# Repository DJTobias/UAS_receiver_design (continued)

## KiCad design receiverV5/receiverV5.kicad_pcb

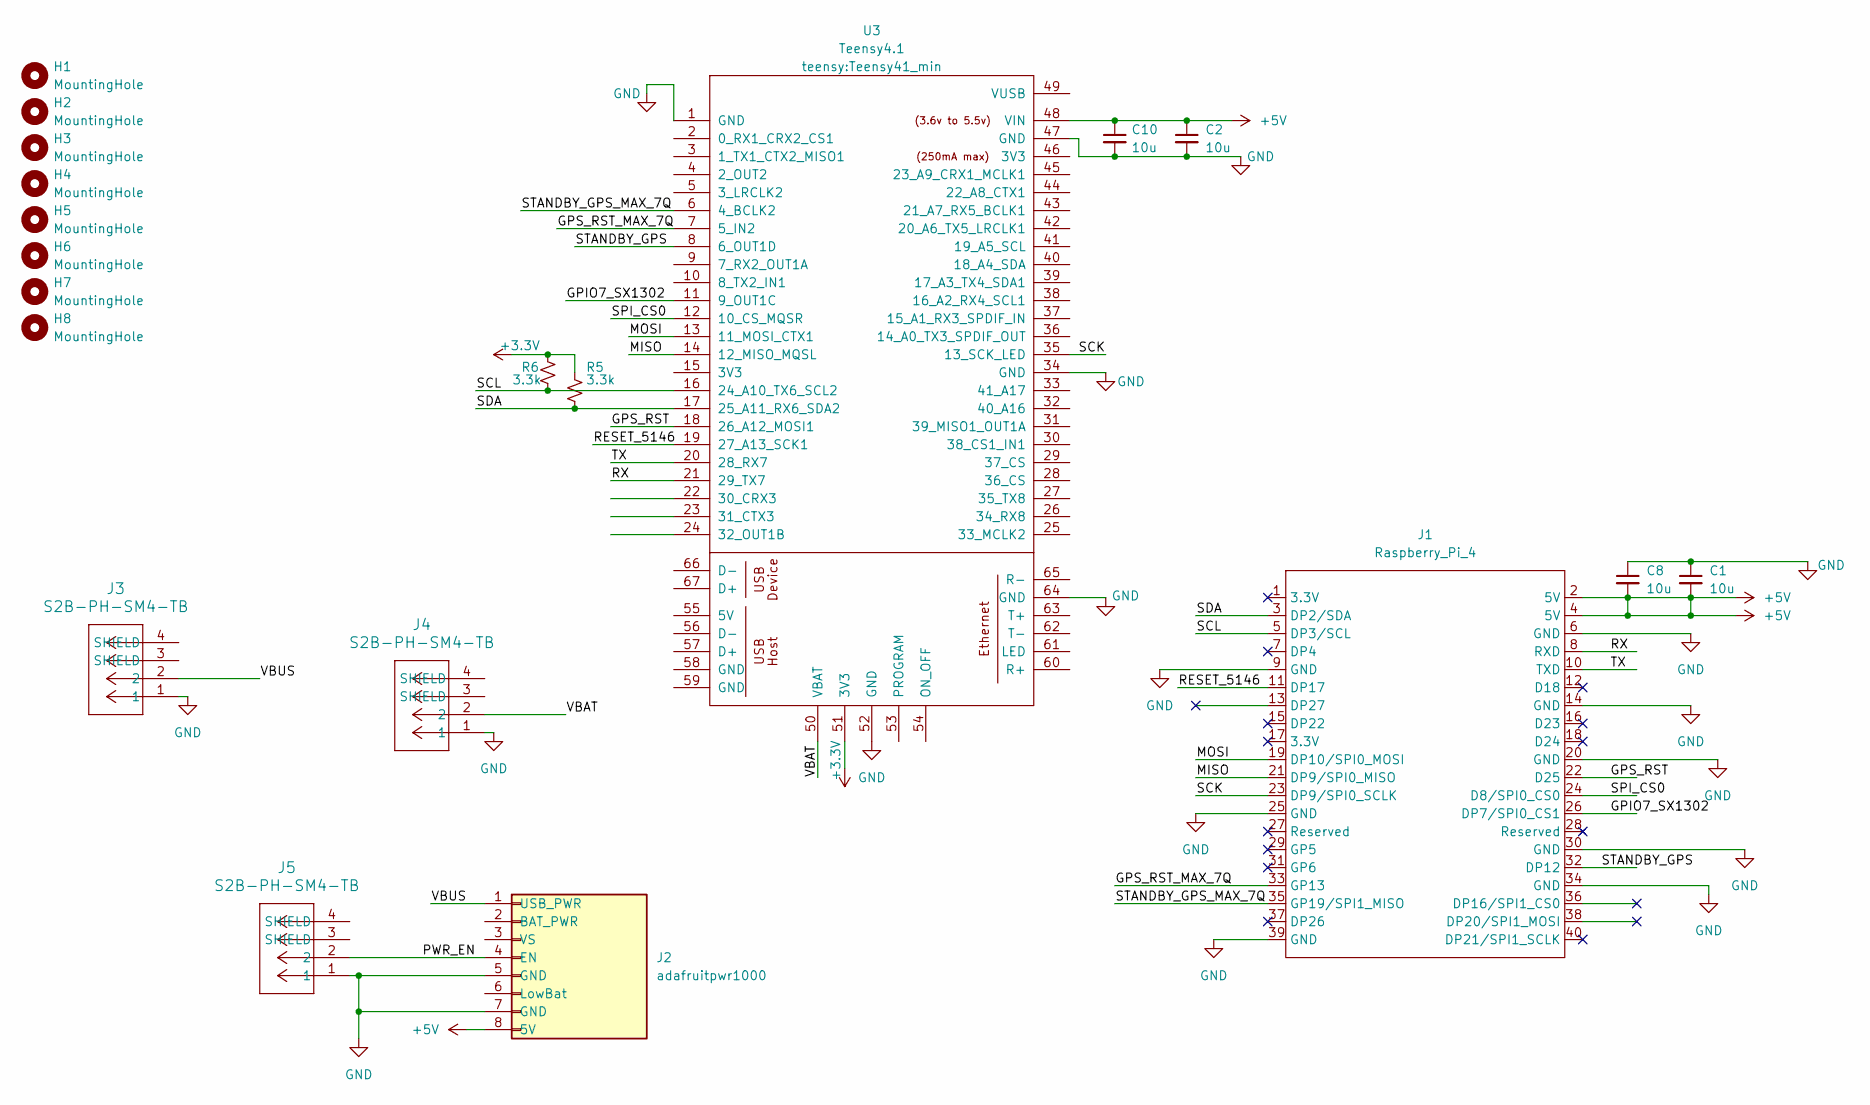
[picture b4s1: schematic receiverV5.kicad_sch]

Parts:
C1, C2, C8, C10: 10u; C_1206_3216Metric_Pad1.33x1.80mm_HandSolder
H1, H2, H3, H4: MountingHole; mountinghole3mm
H5: MountingHole; MountingHole_4mm_t4
H6, H7, H8: MountingHole; mountinghole4mm
J1: Raspberry_Pi_4; PinHeader_2x20_P2.54mm_Vertical
J2: adafruitpwr1000; adafruit powerboost 1000
J3, J4, J5: S2B-PH-SM4-TB; CONN_S2B-PH-SM4-TB_JST_mod2
R5, R6: 3.3k; R_1206_3216Metric_Pad1.30x1.75mm_HandSolder
U3: Teensy4.1; Teensy41_min

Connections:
+3.3V: R5.1, R6.1, U3.51 (3V3)
+5V: C1.2, C2.1, C8.2, C10.1, J1.2 (5V), J1.4 (5V), J2.8 (5V), U3.48 (VIN)
/GPIO7_SX1302: J1.26 (DP7/SPI0_CS1), U3.11 (9_OUT1C)
/GPS_RST: J1.22 (D25), U3.18 (26_A12_MOSI1)
/GPS_RST_MAX_7Q: J1.33 (GP13), U3.7 (5_IN2)
/MISO: J1.21 (DP9/SPI0_MISO), U3.14 (12_MISO_MQSL)
/MOSI: J1.19 (DP10/SPI0_MOSI), U3.13 (11_MOSI_CTX1)
/PWR_EN: J2.4 (EN), J5.2
/RESET_5146: J1.11 (DP17), U3.19 (27_A13_SCK1)
/RX: J1.8 (RXD), U3.21 (29_TX7)
/SCK: J1.23 (DP9/SPI0_SCLK), U3.35 (13_SCK_LED)
/SCL: J1.5 (DP3/SCL), R6.2, U3.16 (24_A10_TX6_SCL2)
/SDA: J1.3 (DP2/SDA), R5.2, U3.17 (25_A11_RX6_SDA2)
/SPI_CS0: J1.24 (D8/SPI0_CS0), U3.12 (10_CS_MQSR)
/STANDBY_GPS: J1.32 (DP12), U3.8 (6_OUT1D)
/STANDBY_GPS_MAX_7Q: J1.35 (GP19/SPI1_MISO), U3.6 (4_BCLK2)
/TX: J1.10 (TXD), U3.20 (28_RX7)
/VBAT: J4.2, U3.50 (VBAT)
/VBUS: J2.1 (USB_PWR), J3.2
GND: C1.1, C2.2, C8.1, C10.2, J1.6 (GND), J1.9 (GND), J1.14 (GND), J1.20 (GND), J1.25 (GND), J1.30 (GND), J1.34 (GND), J1.39 (GND), J2.5 (GND), J2.7 (GND), J3.1, J4.1, J5.1, U3.1 (GND), U3.34 (GND), U3.47 (GND), U3.52 (GND), U3.64 (GND)

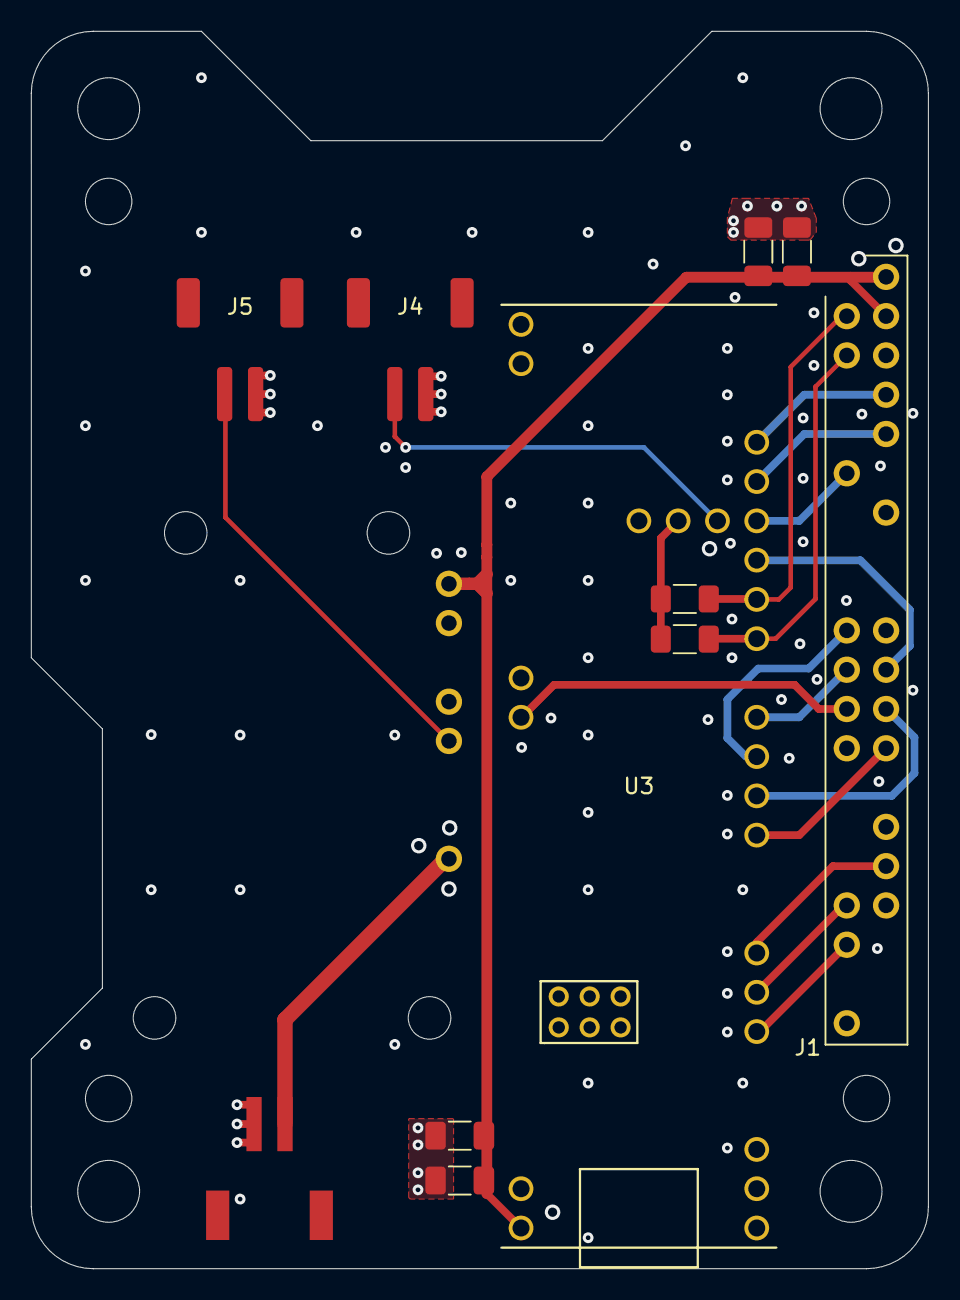
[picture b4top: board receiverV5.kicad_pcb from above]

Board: 4 copper layers, 58.0 x 80.0 mm, 20 parts (0 on the bottom side), 20 nets.

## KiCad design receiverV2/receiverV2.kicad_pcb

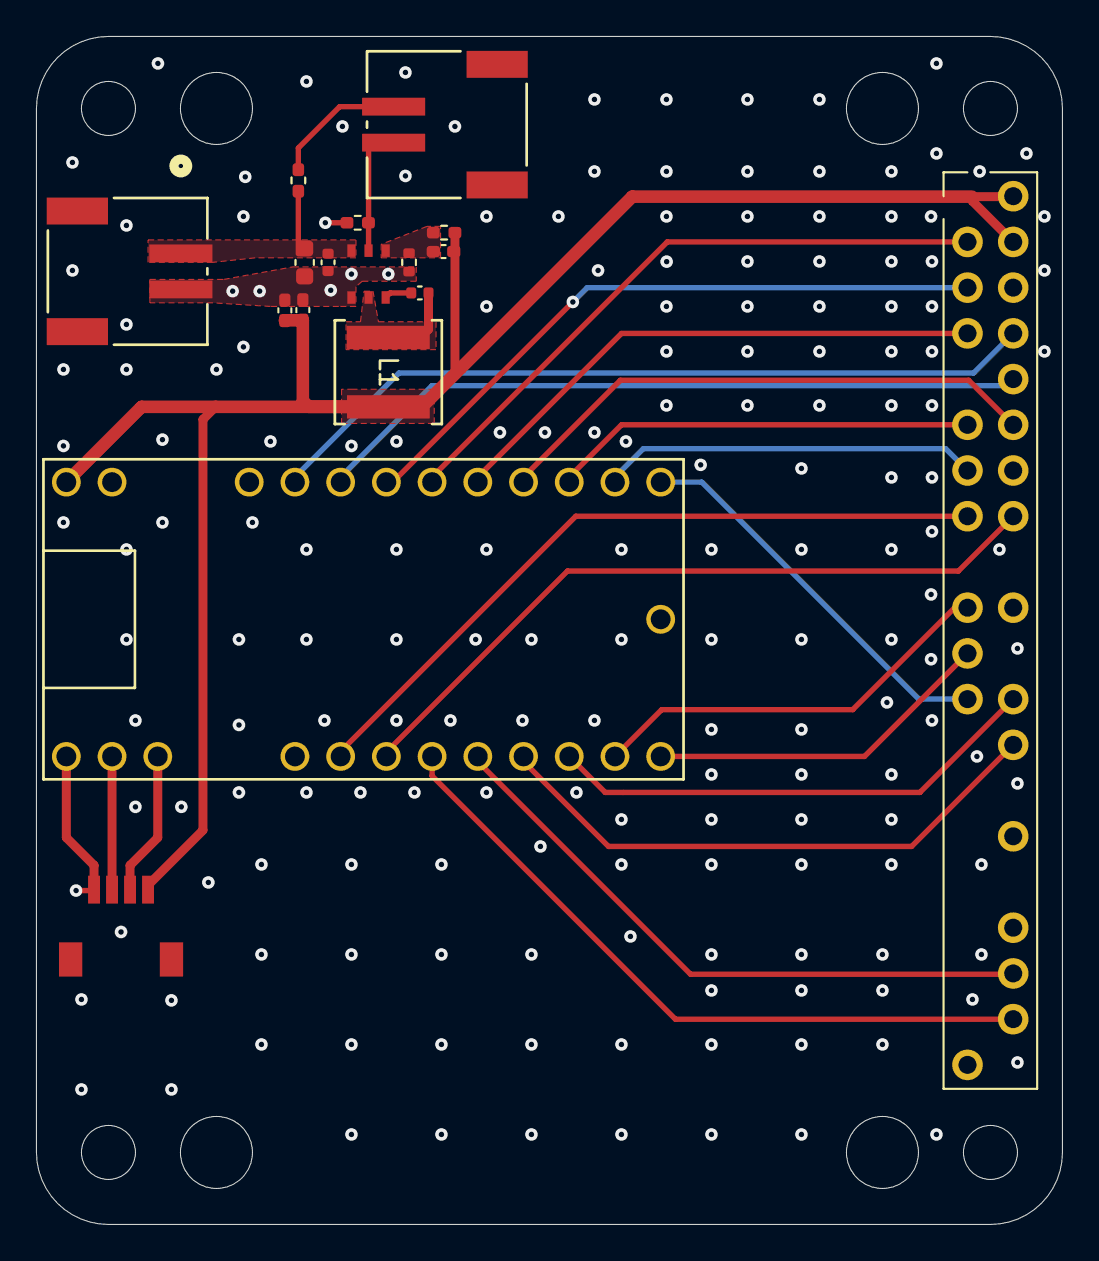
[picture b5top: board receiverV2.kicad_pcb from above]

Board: 4 copper layers, 57.0 x 66.0 mm, 25 parts (0 on the bottom side), 27 nets.

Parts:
C1: 10u; C_0603_1608Metric
C2, C3: 100n; C_0402_1005Metric
C4, C5: 22u; C_0402_1005Metric_Pad0.74x0.62mm_HandSolder
C6: 47p; C_0402_1005Metric_Pad0.74x0.62mm_HandSolder
H1, H2, H3, H4: MountingHole; MountingHole_3mm_rec
H5, H6, H7, H8: MountingHole; MountingHole_4mm_t4
J1: Raspberry_Pi_4; PinHeader_2x20_P2.54mm_Vertical_receiver
J2: SM04B-SRSS-TB; CONN_SM04B-SRSS-TB_JST
J3: S2B-PH-SM4-TB; CONN_S2B-PH-SM4-TB_JST
L1: 6.8uH; IND_SRP5050FA-5R6M_BRN_mod
On/Off/switch1: S2B-PH-SM4-TB; CONN_S2B-PH-SM4-TB_JST_no_circle
R1, R2: 100k; R_0402_1005Metric_Pad0.72x0.64mm_HandSolder
R3: 162k; R_0402_1005Metric_Pad0.72x0.64mm_HandSolder
R4: 31.1k; R_0402_1005Metric
U1: Teensy4.0; Teensy40_receiver
U2: AP63300WU-7_mod; SOIC_05WU-7_DIO-L_mod

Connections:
+5V: C4.1, C5.1, C6.2, J1.2 (5V), J1.4 (5V), J2.4, L1.2, R3.2, U1.33 (VIN)
/BUSY: J1.7 (DP4), U1.24 (17_A3_TX4_SDA1)
/CS0: J1.24 (D8/SPI0_CS0), U1.12 (10_CS_MQSR)
/CS1: J1.26 (DP7/SPI0_CS1), U1.11 (9_OUT1C)
/DC-DC-Out: C3.2, L1.1, U2.5 (SW)
/DIO1: J1.11 (DP17), U1.22 (15_A1_RX3_SPDIF_IN)
/Enable: On/Off/switch1.1, R1.1, U2.2 (EN)
/FB: C6.1, R3.1, R4.1, U2.1 (FB)
/GPS_STBY: J1.13 (DP27), U1.21 (14_A0_TX3_SPDIF_OUT)
/LO_RST: J1.15 (DP22), U1.7 (5_IN2)
/MISO: J1.21 (DP9/SPI0_MISO), U1.14 (12_MISO_MQSL)
/MOD_6_MULT: J1.38 (DP20/SPI1_MOSI), U1.9 (7_RX2_OUT1A)
/MOD_8_MULT: J1.36 (DP16/SPI1_CS0), U1.10 (8_TX2_IN1)
/MOD_RST: J1.16 (D23), U1.8 (6_OUT1D)
/MOSI: J1.19 (DP10/SPI0_MOSI), U1.13 (11_MOSI_CTX1)
/RAD_PWR: J1.12 (D18), U1.23 (16_A2_RX4_SCL1)
/RX: J1.8 (RXD), U1.28 (21_A7_RX5_BCLK1)
/RX_ALT: J2.2, U1.2 (0_RX1_CRX2_CS1)
/SCK: J1.23 (DP9/SPI0_SCLK), U1.20 (13_SCK_CRX1_LED)
/SCL: J1.5 (DP3/SCL), U1.26 (19_A5_SCL0)
/SDA: J1.3 (DP2/SDA), U1.25 (18_A4_SDA0)
/TX: J1.10 (TXD), U1.27 (20_A6_TX5_LRCLK1)
/TX_ALT: J2.3, U1.3 (1_TX1_CTX2_MISO1)
GND: C1.2, C2.2, C4.2, C5.2, J1.6 (GND), J1.14 (GND), J1.20 (GND), J1.30 (GND), J1.34 (GND), J1.39 (GND), J2.1, J3.2, R1.2, R4.2, U1.1 (GND), U1.17 (GND), U1.32 (GND), U2.4 (GND)
unnamed: On/Off/switch1.2, R2.1
unnamed: C3.1, U2.6 (BST)
VBUS: C1.1, C2.1, J3.1, R2.2, U2.3 (VIN)

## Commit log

2024-12-05 add .gitignore
2024-12-05 add receiver kicad files
2025-05-28 add teensy4.1 version of receiver
2025-07-23 update receiver repo
2025-08-22 add rp2350 design
2025-08-27 add rp2350V2
2025-09-25 add panelized files
2025-09-27 update to schematic
2025-10-08 updates to receiver layout
2025-10-22 add pdf of design and changes to board
2026-02-13 add receiver V3 and V4
2026-02-13 added changes to v4
2026-05-13 addev initial v5 version
2026-05-14 working drc for v5
